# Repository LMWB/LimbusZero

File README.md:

# LimbusZero
Custom Microcontroller Board based on STM32C0-Series

# Features
- STM32C031K6T6 Microcontroller
- ST M24C01 I2C EEPROM
- no crystal oscillator since this board uses STM32 build in 48MHz HSI48RC clock generator
    - accuracy needs to be discussed but since software is working fine I guess there will be no dramatic issus 
- Power indicator LED
- USB mini as power supply NO DATA!
- User LED
- 2.54mm Pin Headers that would fit on regular breadbords for rapid prototyping
- debug / programming interface according to STLink that comes with most of STM32 Nucleo Boards

# Firmware
There is quite extensive demo I developed for Emil's Birthday using the [breadbord-IO](https://github.com/LMWB/BreadboardIO) and a [neopixel](https://www.az-delivery.de/products/kopie-von-rgb-led-ring-ws2812-mit-12-rgb-leds-5v-fuer-arduino?_pos=3&_psq=led+&_ss=e&_v=1.0) ring in the software sub folder. It's written in C and uses the STM32-HAL and STM32-cubeIDE. Look closely, main-loop is empty since all features and peripherals are controlled by interrupts so the user section `while(1){}` remains untouched. 

# Todo
- add user button

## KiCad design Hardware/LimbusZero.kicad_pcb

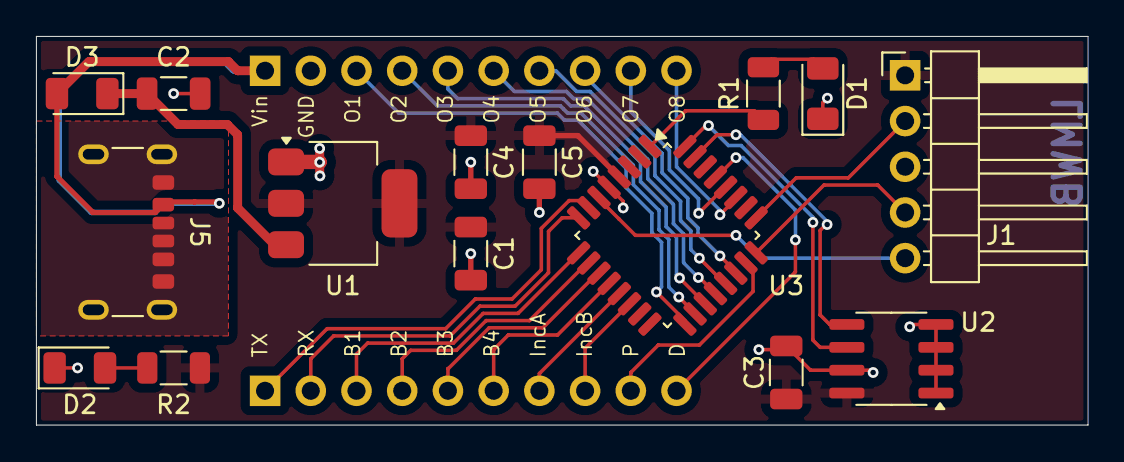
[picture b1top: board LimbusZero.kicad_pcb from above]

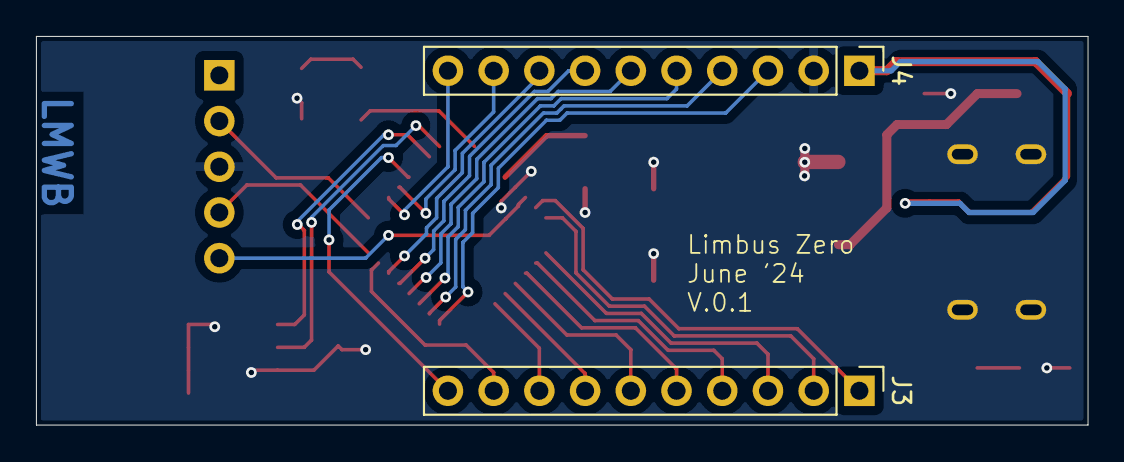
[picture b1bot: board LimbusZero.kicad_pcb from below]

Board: 2 copper layers, 58.4 x 21.6 mm, 17 parts (2 on the bottom side), 30 nets.

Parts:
C1, C2: 1u; C_1206_3216Metric
C3, C5: 100n; C_1206_3216Metric
C4: 4.7u; C_1206_3216Metric
D1, D2: LED; LED_1206_3216Metric
D3: D; D_1206_3216Metric
J1: Conn_01x05; PinHeader_1x05_P2.54mm_Horizontal
J3, J4: Conn_01x10; PinHeader_1x10_P2.54mm_Vertical
J5: USB_C_Receptacle_PowerOnly_6P; USB_C_Receptacle_GCT_USB4125-xx-x-0190_6P_TopMnt_Horizontal
R1, R2: 220; R_1206_3216Metric
U1: AMS1117-3.3; SOT-223-3_TabPin2
U2: M24C01-FMN; SOIC-8_3.9x4.9mm_P1.27mm
U3: STM32C031K6T6; LQFP-32_7x7mm_P0.8mm

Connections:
+3V3: C1.1, C3.2, C4.1, C5.1, J1.1, R2.2, U1.2 (VO), U2.8 (VCC), U3.4 (VDD/VDDA)
/B1: J3.3, U3.9 (PA2)
/B2: J3.4, U3.10 (PA3)
/B3: J3.5, U3.11 (PA4)
/B4: J3.6, U3.12 (PA5)
/I2C1_SCL: U2.6 (SCL), U3.32 (PB8)
/I2C1_SDA: U2.5 (SDA), U3.31 (PB7)
/IncA: J3.7, U3.13 (PA6)
/IncB: J3.8, U3.14 (PA7)
/LED1: R1.2, U3.1 (PB9)
/NRST: J1.5, U3.6 (PF2-NRST)
/Out1: J4.3, U3.17 (PB2)
/Out2: J4.4, U3.18 (PA8)
/Out3: J4.5, U3.19 (PA9)
/Out4: J4.6, U3.20 (PC6)
/Out5: J4.7, U3.21 (PA10)
/Out6: J4.8, U3.22 (PA11[PA9])
/Out7: J4.10, U3.27 (PB3)
/Out8: J4.9, U3.28 (PB4)
/Poti1: J3.9, U3.23 (PA12[PA10])
/SPI1_MOSI: J3.10, U3.29 (PB5)
/SYS_SWCLK: J1.2, U3.25 (PA14)
/SYS_SWDIO: J1.4, U3.24 (PA13)
/UART1_RX: J3.2, U3.8 (PA1)
/UART1_TX: J3.1, U3.7 (PA0)
/Vbus: D3.2 (A), J4.1, J5.A9 (VBUS), J5.B9 (VBUS)
/Vin: C2.1, D3.1 (K), U1.3 (VI)
GND: C1.2, C2.2, C3.1, C4.2, C5.2, D1.1 (K), D2.1 (K), J1.3, J4.2, J5.A12 (GND), J5.B12 (GND), J5.S1 (SHIELD), U1.1 (GND), U2.1 (E0), U2.2 (E1), U2.3 (E2), U2.4 (VSS), U2.7 (~WC), U3.5 (VSS/VssA)
unnamed: D1.2 (A), R1.1
unnamed: D2.2 (A), R2.1

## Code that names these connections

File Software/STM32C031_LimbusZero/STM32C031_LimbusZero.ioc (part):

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Mcu.Name=STM32C031K(4-6)Tx
Mcu.Package=LQFP32
Mcu.UserName=STM32C031K6Tx
PA0.Mode=Asynchronous
PA0.Signal=USART1_TX
PA1.Mode=Asynchronous
PA1.Signal=USART1_RX
PA10.GPIOParameters=GPIO_Label
PA10.GPIO_Label=Out5
PA10.Signal=GPIO_Output
PA11\ [PA9].GPIOParameters=GPIO_Label
PA11\ [PA9].GPIO_Label=Out6
PA11\ [PA9].Signal=GPIO_Output
PA12\ [PA10].GPIOParameters=GPIO_PuPd,GPIO_Label
PA12\ [PA10].GPIO_Label=Poti1
PA12\ [PA10].GPIO_PuPd=GPIO_NOPULL
PA12\ [PA10].Mode=IN12
PA12\ [PA10].Signal=ADC1_IN12
PA13.Mode=Serial_Wire
PA13.Signal=DEBUG_SWDIO
PA14-BOOT0.Mode=Serial_Wire
PA14-BOOT0.Signal=DEBUG_SWCLK
PA2.GPIOParameters=GPIO_PuPd,GPIO_Label,GPIO_ModeDefaultEXTI
PA2.GPIO_Label=B1
PA2.GPIO_ModeDefaultEXTI=GPIO_MODE_IT_FALLING
PA2.GPIO_PuPd=GPIO_PULLUP
PA2.Signal=GPXTI2
PA3.GPIOParameters=GPIO_PuPd,GPIO_Label,GPIO_ModeDefaultEXTI
PA3.GPIO_Label=B2
PA3.GPIO_ModeDefaultEXTI=GPIO_MODE_IT_FALLING
PA3.GPIO_PuPd=GPIO_PULLUP
PA3.Signal=GPXTI3
PA4.GPIOParameters=GPIO_PuPd,GPIO_Label,GPIO_ModeDefaultEXTI
PA4.GPIO_Label=B3
PA4.GPIO_ModeDefaultEXTI=GPIO_MODE_IT_FALLING
PA4.GPIO_PuPd=GPIO_PULLUP
PA4.Signal=GPXTI4
PA5.GPIOParameters=GPIO_PuPd,GPIO_Label,GPIO_ModeDefaultEXTI
PA5.GPIO_Label=B4
PA5.GPIO_ModeDefaultEXTI=GPIO_MODE_IT_FALLING
PA5.GPIO_PuPd=GPIO_PULLUP
PA5.Signal=GPXTI5
PA6.GPIOParameters=GPIO_PuPd,GPIO_Label,GPIO_ModeDefaultEXTI
PA6.GPIO_Label=IncA
PA6.GPIO_ModeDefaultEXTI=GPIO_MODE_IT_FALLING
PA6.GPIO_PuPd=GPIO_PULLUP
PA6.Signal=GPXTI6
PA7.GPIOParameters=GPIO_PuPd,GPIO_Label
PA7.GPIO_Label=IncB
PA7.GPIO_PuPd=GPIO_PULLUP
PA7.Signal=GPIO_Input
PA8.GPIOParameters=GPIO_Label
PA8.GPIO_Label=Out2
PA8.Signal=GPIO_Output
PA9.GPIOParameters=GPIO_Label
PA9.GPIO_Label=Out3
PA9.Signal=GPIO_Output
PB2.GPIOParameters=GPIO_Label
PB2.GPIO_Label=Out1
PB2.Signal=GPIO_Output
PB3.GPIOParameters=GPIO_Label
PB3.GPIO_Label=Out8
PB3.Signal=GPIO_Output
PB4.GPIOParameters=GPIO_Label
PB4.GPIO_Label=Out7
PB4.Signal=GPIO_Output
PB5.Mode=TX_Only_Simplex_Unidirect_Master
PB5.Signal=SPI1_MOSI
PB6.GPIOParameters=GPIO_Speed,GPIO_PuPd
PB6.GPIO_PuPd=GPIO_PULLDOWN
PB6.GPIO_Speed=GPIO_SPEED_FREQ_HIGH
PB6.Mode=TX_Only_Simplex_Unidirect_Master
PB6.Signal=SPI1_SCK
PB7.Mode=I2C
PB7.Signal=I2C1_SDA
PB8.Mode=I2C
PB8.Signal=I2C1_SCL
PB9.GPIOParameters=GPIO_Label
PB9.GPIO_Label=Onboard_LED
PB9.Signal=S_TIM17_CH1
PC6.GPIOParameters=GPIO_Label
PC6.GPIO_Label=Out4
PC6.Signal=GPIO_Output
RCC.HSE_VALUE=8000000
RCC.SYSCLKFreq_VALUE=48000000
board=custom

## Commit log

2024-07-13 Create readme.md for Emils Birthda
2024-07-15 pimp readme add pics
2024-07-15 pimp readme
2024-07-15 pimp readme add schematics and sub folders
2024-07-15 added software and hardware sources
2024-07-21 readme.md aktualisieren
2024-07-22 added stuff to readme
2025-06-02 backup kicad files
2025-06-02 started work on version with C092
